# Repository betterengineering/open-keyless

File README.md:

# Open Keyless

Open Keyless is a keyless entry system for contactless key cards. This project includes all of the necessary software,
printed circuit board designs, 3D models, and documentation to build an RFID based badge reader and controller.

Note: this project is under development and has not yet been completed. Once a functioning version of this
project exists, this message will be removed and the release will be added as a github release.

## Installation
To install the latest release, run the following from your Raspberry Pi:
```
curl -LO https://github.com/betterengineering/open-keyless/releases/latest/download/install.sh
chmod +x ./install.sh
sudo ./install.sh
```

## Documentation
The documentation for Open Keyless is kept in the repo! Checkout the [Overview](docs/overview.md) for a starting point.

## Development
This project uses Go 1.11 modules! If you have Go 1.11 or later installed, no other project setup is necessary.

### Testing
To run tests locally, run the following:
```bash
make test
```

To include integration tests, run the following:
```bash
make test-full
```

### Mocks
This project uses Golang's [mockgen](https://github.com/golang/mock) tool to generate mocks for interfaces. To regenerate mocks, run the following:
```bash
make mocks
```

### Libnfc
To develop locally, you will need libnfc installed. I would like to remove this as a dependency in the future, but alas,
it is a dependency for now.

For MacOS, run the following:
```bash
brew install libnfc
```

For Debian based Linux distros, run the following:
```bash
apt-get install -y libnfc-dev
```

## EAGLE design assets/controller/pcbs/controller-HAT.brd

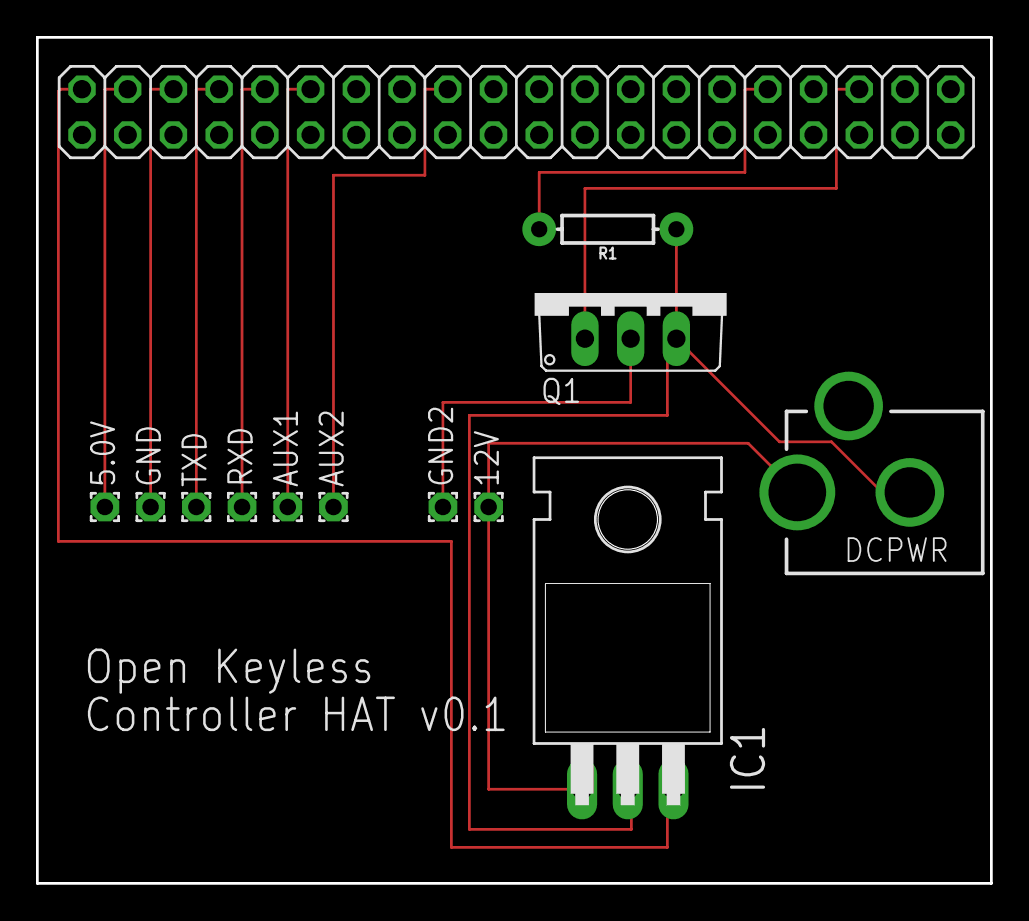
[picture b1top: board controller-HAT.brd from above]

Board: 2 copper layers, 53.0 x 47.0 mm, 13 parts (0 on the bottom side), 12 nets.

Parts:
5.0V, 12V: 1,6/0,9
AUX1, AUX2: 1,6/0,9
DCPWR: DCJACK_2MM_PTH
GND, GND2: 1,6/0,9
GPIO: 2X20
IC1: 7805T; TO220H
Q1: TO220V
R1: 100; AXIAL-0.3
RXD: 1,6/0,9
TXD: 1,6/0,9

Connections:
unnamed: GND2.1, Q1.2
unnamed: 12V.1, DCPWR.PWR, IC1.1
unnamed: GPIO.32, R1.P$2
unnamed: DCPWR.GND, IC1.2, Q1.3, R1.P$1
unnamed: GPIO.36, Q1.1
unnamed: 5.0V.1, GPIO.4
unnamed: GND.1, GPIO.6
unnamed: GPIO.8, TXD.1
unnamed: GPIO.10, RXD.1
unnamed: AUX1.1, GPIO.12
unnamed: AUX2.1, GPIO.18
unnamed: GPIO.2, IC1.3

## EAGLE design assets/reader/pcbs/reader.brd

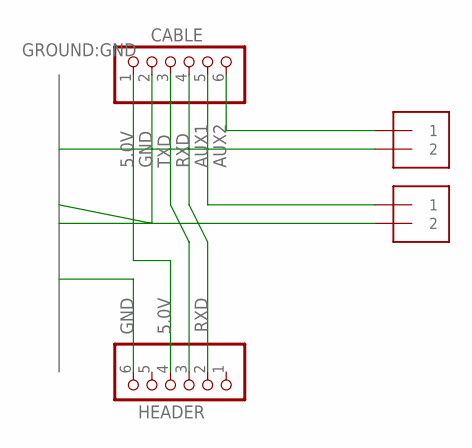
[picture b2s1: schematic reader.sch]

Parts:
AUX1, AUX2: 1X2-3.5MM
CABLE: PINHD-1X6; 1X06
HEADER: PINHD-1X6; 1X06

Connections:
5.0V: CABLE.1, HEADER.4
AUX1: AUX1.1, CABLE.5
AUX2: AUX2.1, CABLE.6
GND: AUX1.2, AUX2.2, CABLE.2, HEADER.6
RXD: CABLE.4, HEADER.2
TXD: CABLE.3, HEADER.3

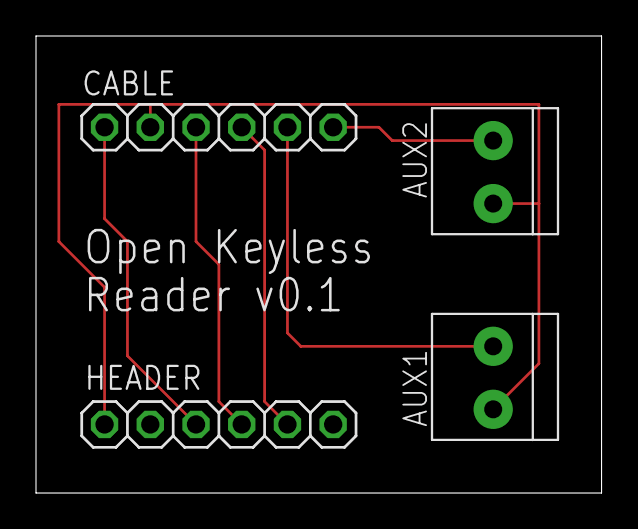
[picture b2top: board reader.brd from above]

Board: 2 copper layers, 31.4 x 25.4 mm, 4 parts (0 on the bottom side), 6 nets.

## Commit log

2019-01-22 Added a package for an electric strike.
    This commit adds infrastructure for mocks and adds a package for an electric
    strike with an implementation for the Raspberry pi.
2019-01-26 Added base drone build.
    This commit adds a build configuration file for drone CI:
    https://cloud.drone.io and updates the Makefile for testing and building the
    Open Keyless Controller.
2019-02-02 Added scanner pacage for RFID badge scanners.
    This commit adds a package and interface for RFID badge scanners.
2019-02-02 Fixed build.
    This commit installs the development package for libnfc so that the project can
    compile and execute tests.
2019-02-08 Added v0.1 assets.
    This commit adds the version 0.1 hardware designs for Open Keyless with the
    exception of the controller housing that is still being designed. Additionally,
    this commit adds a blurb about versioning to the readme.
2019-02-08 Added documentation.
    This commit adds baseline documentation for what this project is and how to use
    it. There are several TODOs that will need to be completed before this project
    can be released.
2019-02-09 Added debian packaging.
    This commit adds debian packaging to this project. The resulting debian package
    contains the go binary compiled for ARM and a systemd unit file.
2019-02-10 Added datastore package and airflow implentation.
    This commit adds a datastore package to interact with badges and adds an
    implementation for airflow.
2019-02-16 Updated build to cross compile.
    This commit updates the build to cross compile a static binary for armhf. This
    will allow building on Drone CI amd64 agents for raspbian.
2019-02-16 Added the controller application.
    This commit creates the initial implementation of the controller application
    that interacts with the datastore, strike, and badge scanner.
2019-02-16 Dropped compilation to ARMv6.
    This commit switches the ARM architecture to use ARMv6 to support the Raspberry
    Pi Zero W as well as the Raspberry PI 3.
2019-02-16 WIP 2
2019-02-16 WIP 3
2019-02-16 Set explicit dir
2019-02-16 Remove linker flag.
2019-02-16 try again
2019-02-16 remove flag
2019-02-16 Test
2019-02-16 Williams space
2019-02-16 Add cmake find root
2019-02-16 another
2019-02-23 Added an application package.
    This commit adds an application package to provide metrics and logging for
    Open Keyless based applications.
2019-02-23 Added better logging.
    This commit adds better logging for the Open Keyless Controller.
2019-02-23 Added access metrics.
    This commit adds counters for access granted and access denied.
2019-02-26 WIP buzzer
2019-02-26 Fixup pin name
2019-02-26 try other gpio type
2019-02-26 Updated the controller hat.
    This commit updates the controller hat to include a voltage regulator. This will
    allow a single, 12v power source to power both the strike and the raspberry pi
    through the 5v pin.
2019-11-05 Updated dependencies.
2019-11-05 Updated build.
    Updated build to use go 1.13 and new Google Cloud bucket.
2019-11-05 Added base server with auth.
    This commit adds a server package with a configured gin-gonic API with
    auth.
2019-11-05 Fixed mock generation.
    This commit fixes mock generation. The periph was not originally setup
    properly. This commit removes the ability to regenerate in favor of not
    having to fuss with it.
2019-11-05 Added keyval interface with redis implementation.
    This commit adds a keyval package with a redis implementation and mock.
2019-11-05 Added base development structure.
    This commit adds a base development structure for shop manager.
2021-06-02 Fixed imports.
    I changed my username on Github. This commit updates the imports to
    match.
2021-06-27 Added HID Scanner and TextFile datastore support.
    This commit adds support for the USB badge reader at the shop and
    support for a text file based datastore.
2021-06-27 Remove integration test.
    This commit removes the airtable integration test so that this project
    will build again.
2021-06-27 Removed config requirements for Airtable.
    This commit removes config requirements for Airtable so the binary can
    start without the config in place.
2021-06-27 Fix debian build.
    This commit fixes the Debian build. I renamed my username, but Dockerhub
    doesn't change the username.
2021-06-27 Remove Google Cloud Storage upload.
    This commit removes the upload for GCP.
2021-06-27 Added github release
    This commit adds github release and cleans up the build.
2021-06-27 Fix publish
2021-06-27 Fix versioning
2021-06-27 Added an install script.
    I still need to test this on the device.
2021-06-27 Fix installation instructions
2021-06-27 Fix readme
2023-02-15 Bump github.com/prometheus/client_golang from 0.9.2 to 1.11.1
    Bumps [github.com/prometheus/client_golang](https://github.com/prometheus/client_golang) from 0.9.2 to 1.11.1.
    - [Release notes](https://github.com/prometheus/client_golang/releases)
    - [Changelog](https://github.com/prometheus/client_golang/blob/main/CHANGELOG.md)
    - [Commits](https://github.com/prometheus/client_golang/compare/v0.9.2...v1.11.1)
    ---
    updated-dependencies:
2024-01-09 Update module github.com/prometheus/client_golang to v1 [SECURITY]

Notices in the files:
parts and their libraries:
SparkFun-Resistors: Licensing: Creative Commons ShareAlike 4.0 International - https://creativecommons.org/licenses/by-sa/4.0
